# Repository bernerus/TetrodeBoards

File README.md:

# TetrodeBoards
The Tetrode Boards by Ian White, GM3SEK. Redesigned with KiCad.

In 1998 Ian White, G3SEK, nowadays GM3SEK designed control and protection circuits for RF power amplifiers
that use tube tetrodes. These boards were sold for many years by the designer but were retired around 2017
and are no longer available.

The manuals are still available however, and that documantation is excellent. 

After my retirement as a system developer I found time to return to the VHF DXing that I used to do as a 
student in the late 1970's.
By then one of the things I built was a VHF power amplifier, described by Fred Merry, W2GN, which was used
even for some EME contacts until around 1987 when a storm took my antenna. Since then, the amplifier was
only used occasionally.

Now, 37 years later, the ham world has changed quite a lot. Nowadays computers make the waveforms and almost
every ham has a spectrum analyzer built into their radio. My signals from the old PA didn't look very good there.

Actually it is probaly at miracle that the PA and its power supply worked at all now. There were lots of electrolytic
capacitors in the power supply that were surplus already in the mid 1970's, and when I got reports on hum on my
signal, I checked these caps. I had only about 8 uF left and the G1 and G2 voltage varied too much to be happy with.

That's when I found out that these tetrode boards could help, but since the boards were no longer sold, I decided
to try to re-engineer them using KiCad. This time using methods available today. Thus this design uses SMD mounted
components and professionally produced boards. I have some boards left, so anyone who likes to try building on these
boards can have them for the expense of postage. Beware though that they have issues. Check the issues tab at GitHub first.

A crucial component in Ian's design is the 748 op amp. 
These are no longer manufactured, but they are available at eBay.
Luckily for me, I found a few 748 IC:s leftover from the happy '70s in my old junkbox. 

Christer Bernérus, SM6FBQ. 
JO67BQ 2024-04-04.

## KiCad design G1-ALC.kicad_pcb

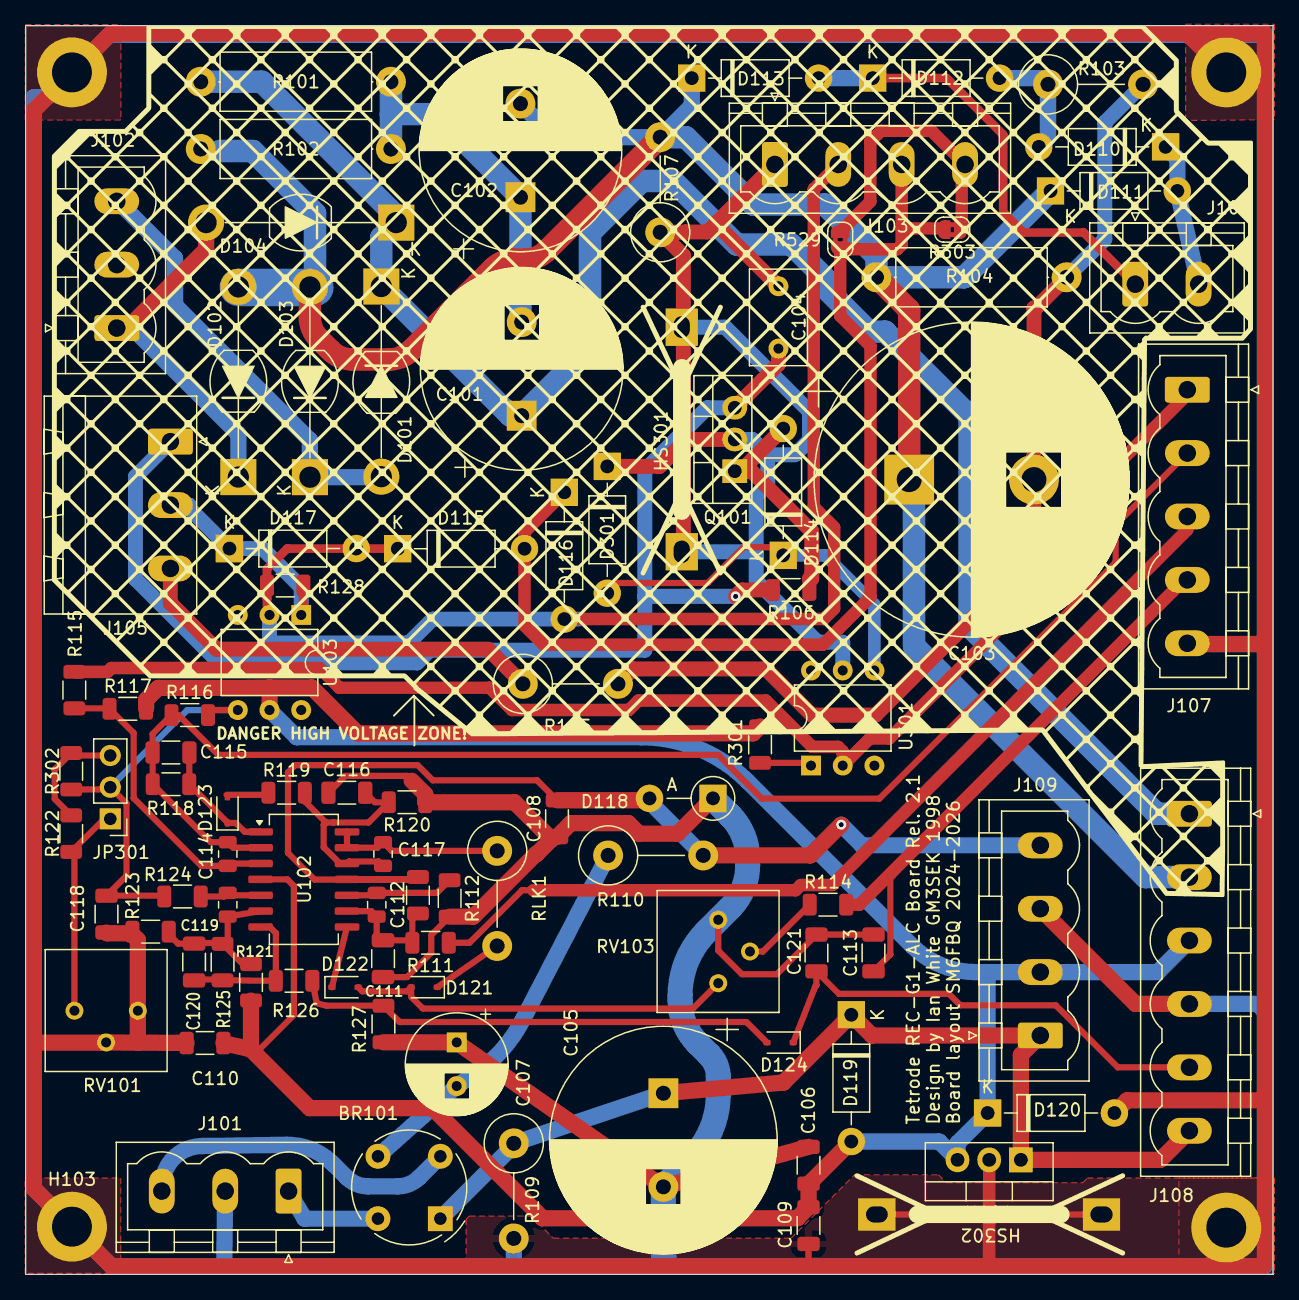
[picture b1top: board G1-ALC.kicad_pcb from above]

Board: 2 copper layers, 100.0 x 100.1 mm, 96 parts (0 on the bottom side), 49 nets.

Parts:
BR101: 2W06; Diode_Bridge_Round_D9.0mm
C101, C102: 100u 350V; CP_Radial_D16.0mm_P7.50mm
C103: 220u 200V; CP_Radial_D25.0mm_P10.00mm_SnapIn
C104: 100n 100V; C_Disc_D7.5mm_W4.4mm_P5.00mm
C105: 4m7 35V; CP_Radial_D18.0mm_P7.50mm
C106, C108, C109, C110, C111, C113, C115, C118, C120, C121: 100n; C_1206_3216Metric
C107: 100u 35V; CP_Radial_D8.0mm_P3.50mm
C112, C114, C117, C119: 33p; C_0805_2012Metric
C116: 1u; C_1206_3216Metric
D101, D102, D103, D104: BY228; D_SOD-64_P15.24mm_big_holes_Horizontal
D110, D111, D112, D113, D115, D116, D117, D119, D120: 1N4007; D_DO-41_SOD81_P10.16mm_Horizontal
D114: BZX85C56; D_DO-41_SOD81_P10.16mm_Horizontal
D118: BZX55C12V; D_DO-41_SOD81_P5.08mm_Vertical_AnodeUp
D121, D122, D123, D124: 1N4148WS; D_SOD-323
D301: 1N5365 36V; D_DO-41_SOD81_P10.16mm_Horizontal
H101, H102, H103, H104: MountingHole_Pad; MountingHole_3.2mm_M3_DIN965_Pad
HS301, HS302: Heatsink_Pad_2Pin; 6025DG_Cooler
J101: Conn_01x03_Pin; PhoenixContact_MSTBVA_2,5_3-G-5,08_1x03_P5.08mm_Vertical
J102: 330VAC; PhoenixContact_MSTBVA_2,5_3-G-5,08_1x03_P5.08mm_Vertical
J103, J109: G1 conn.; PhoenixContact_MSTBVA_2,5_4-G-5,08_1x04_P5.08mm_Vertical
J104: 105VAC in; PhoenixContact_MSTBVA_2,5_2-G-5,08_1x02_P5.08mm_Vertical
J105: Conn_01x03_Pin; PhoenixContact_MSTBA_2,5_3-G-5,08_1x03_P5.08mm_Horizontal
J107: Conn_01x05_Pin; PhoenixContact_MSTBVA_2,5_5-G-5,08_1x05_P5.08mm_Vertical
J108: G2 Control board interconnect; PhoenixContact_MSTBVA_2,5_6-G-5,08_1x06_P5.08mm_Vertical
JP301: ALC tune; PinHeader_1x03_P2.54mm_Vertical
Q101: TIP122; TO-220-3_Vertical
R101, R102, R104: 100k 2W; R_Axial_DIN0414_L11.9mm_D4.5mm_P15.24mm_Horizontal
R103: 1k5 2W; R_Axial_DIN0414_L11.9mm_D4.5mm_P7.62mm_Vertical
R105: 3k3 2W; R_Axial_DIN0414_L11.9mm_D4.5mm_P7.62mm_Vertical
R106, R122: 470R; R_1206_3216Metric
R107, R109: 4k7 2W; R_Axial_DIN0414_L11.9mm_D4.5mm_P7.62mm_Vertical
R110: 470R 1W; R_Axial_DIN0414_L11.9mm_D4.5mm_P7.62mm_Vertical
R111, R112, R115, R116, R121, R124: 10k; R_1206_3216Metric
R113: 100k; R_1206_3216Metric
R114: 100R; R_1206_3216Metric
R117, R118, R125: 470k; R_1206_3216Metric
R119: 2k7; R_1206_3216Metric
R120: 1M; R_1206_3216Metric
R123, R128: 22k; R_1206_3216Metric
R126: 39k; R_1206_3216Metric
R127: 33k; R_1206_3216Metric
R301: 270R; R_1206_3216Metric
R302: 560R; R_1206_3216Metric
R303, R529: 0; SolderJumper-2_P1.3mm_Bridged2Bar_RoundedPad1.0x1.5mm
RLK1: 0R; R_Axial_DIN0414_L11.9mm_D4.5mm_P7.62mm_Vertical
RV101: 1k; Potentiometer_Bourns_3386P_Vertical
RV103: 10k; Potentiometer_Bourns_3386P_Vertical
U101: LM7812_TO220; TO-220-3_Vertical
U102: LM324; SO-14_5.3x10.2mm_P1.27mm
U103: MCT5211M; DIP-6_W7.62mm
U301: CNY17-4; DIP-6_W7.62mm

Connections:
+12V: C106.1, C109.1, C110.1, D119.2 (A), D120.1 (K), J108.3, J109.2, R117.2, R121.2, R301.1, U101.3 (VO), U102.4 (V+), U103.5
+24V Unreg: BR101.1 (+), C105.1, D119.1 (K), J108.6, J109.1, R109.1, U101.1 (VI)
-12V: C108.2, D118.2 (A), J109.4, R110.2, R113.1, U102.11 (V-)
/18 VAC +: BR101.4, J101.1
/18 VAC -: BR101.2, J101.3
/105 VAC +: D112.1 (K), D113.2 (A), J104.1
/105 VAC -: D110.1 (K), D111.2 (A), J104.2
/330VAC +: D102.1 (K), D104.2 (A), J102.1
/330VAC -: D101.2 (A), D103.1 (K), J102.3
/ALC: C113.1, J107.4, R114.2
/Cathode: C102.2, C103.1, D102.2 (A), D103.2 (A), D111.1 (K), D113.1 (K), J108.2, R102.2, R104.1, R107.2
/Class AB1_L: J107.1, R115.1, U301.2
/G1: J103.4, R303.1, R529.1
/G1 Switch: C104.1, D301.1 (K), HS301.1, HS301.2, J103.1, Q101.2 (C), R107.1, U301.5
/G1 meter +: D115.1 (K), D116.2 (A), D117.2 (A), J103.2, R128.1, U103.2
/G1 meter -: D115.2 (A), D116.1 (K), J103.3, R303.2, R529.2
/G1 trip: C121.2, D124.1 (K), J108.5
/G2 Unreg: C101.1, D101.1 (K), D104.1 (K), J108.1, R101.1
/Ig1: C114.2, C115.1, J107.2, R116.1, R118.1, U102.2 (-)
/Inhibit: J107.3, R111.1
/RV102 Cold: C104.2, J105.1, Q101.3 (E), R106.2
/RV102 Hot: J105.3, R105.1
/RV102 Mid: D117.1 (K), J105.2, R128.2, U103.1
GND: C105.2, C106.2, C107.1, C108.1, C109.2, C110.2, C111.2, C113.2, C116.1, C118.2, C121.1, D118.1 (K), D120.2 (A), H101.1, H102.1, H103.1, H104.1, HS302.1, HS302.2, J101.2, J107.5, J108.4, J109.3, R109.2, R112.2, R120.1, R123.1, R127.1, RV101.2, RV101.3, RV103.3, U101.2 (GND)
unnamed: BR101.3 (-), C107.2, R110.1
unnamed: C101.2, C102.1, R101.2, R102.1
unnamed: C103.2, R103.2, R104.2, R105.2
unnamed: C120.2, R125.2, R126.1, U102.7
unnamed: D110.2 (A), D112.2 (A), R103.1
unnamed: D114.2 (A), Q101.1 (B), R106.1
unnamed: D114.1 (K), D301.2 (A), U301.4
unnamed: D121.2 (A), D122.2 (A), RV103.1
unnamed: D121.1 (K), RLK1.2
unnamed: D122.1 (K), U102.8
unnamed: D123.2 (A), R119.1
unnamed: C115.2, D123.1 (K), R118.2, U102.1
unnamed: D124.2 (A), R126.2, R127.2
unnamed: JP301.1 (A), R122.2, RV101.1
unnamed: JP301.3 (B), R122.1, R302.2
unnamed: C118.1, JP301.2 (C), R116.2, R124.1, R302.1, U103.4
unnamed: R114.1, RV103.2
unnamed: R301.2, U301.1
unnamed: C114.1, R115.2, R117.1, U102.3 (+)
unnamed: C119.1, R124.2, U102.5 (+)
unnamed: C119.2, C120.1, R121.1, R123.2, R125.1, U102.6 (-)
unnamed: C112.1, R112.1, U102.10 (+)
unnamed: C111.1, C112.2, R111.2, R113.2, U102.9 (-)
unnamed: C116.2, C117.1, R119.2, R120.2, U102.12 (+)
unnamed: C117.2, RLK1.1, U102.13 (-), U102.14

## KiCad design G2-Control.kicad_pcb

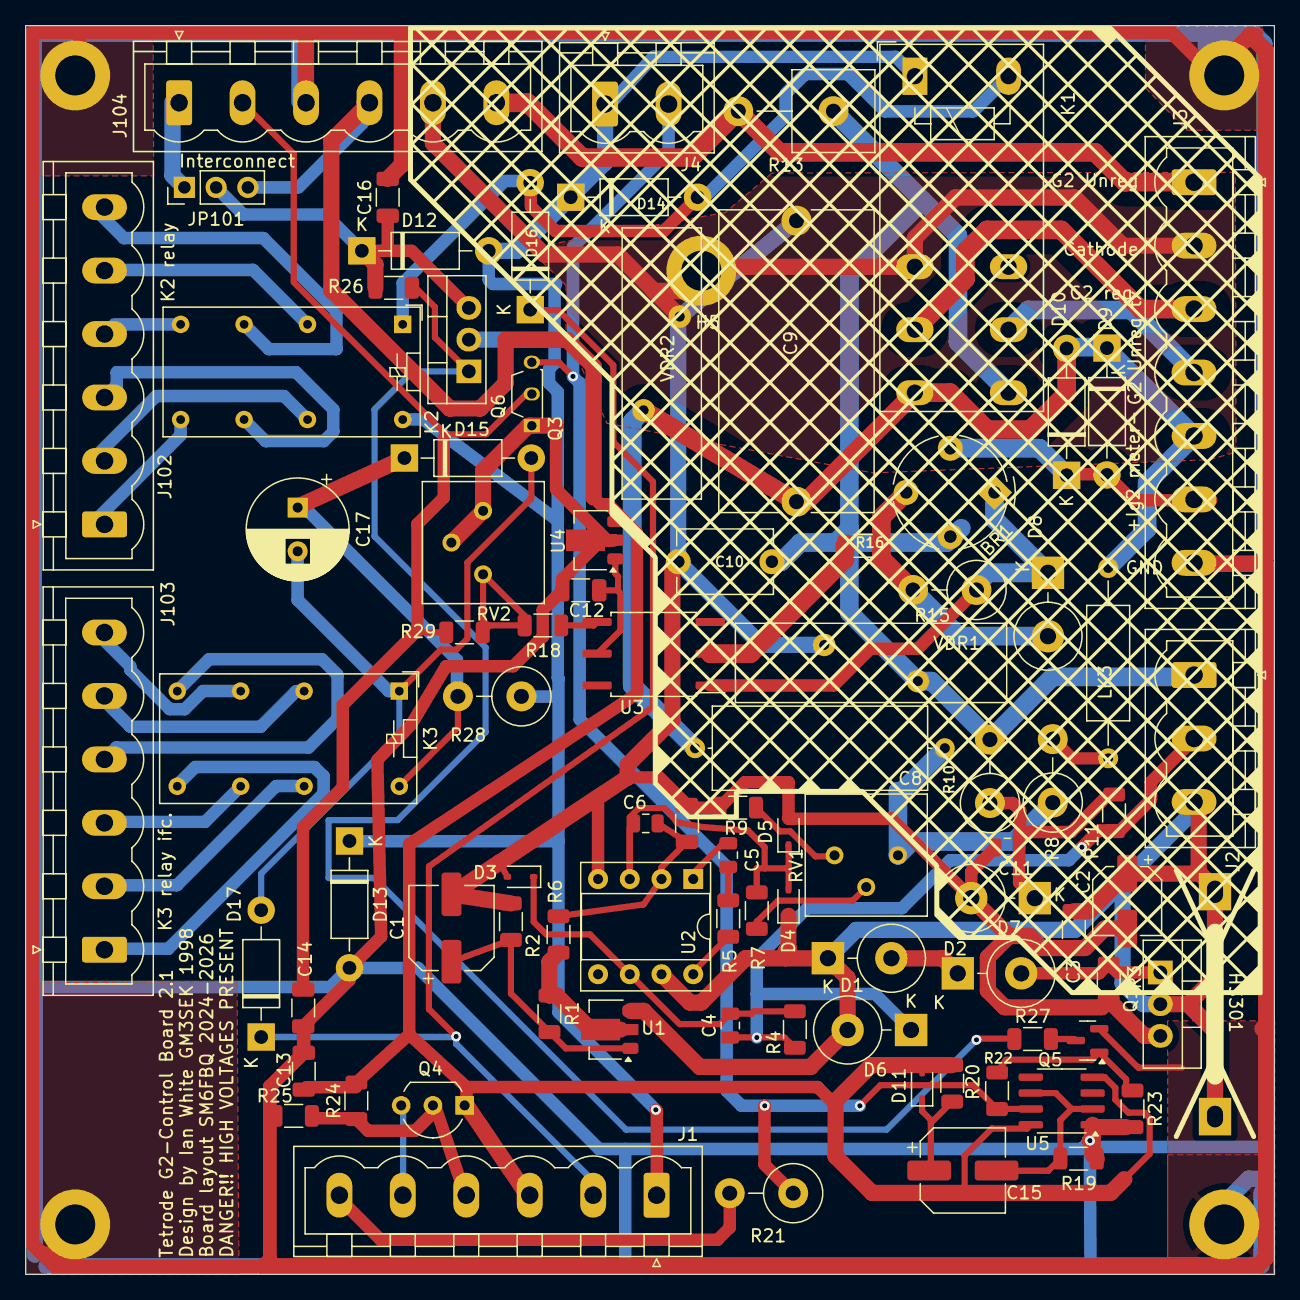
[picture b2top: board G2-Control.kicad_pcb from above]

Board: 2 copper layers, 100.0 x 100.0 mm, 93 parts (0 on the bottom side), 61 nets.

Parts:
BR1: 2W06; Diode_Bridge_Round_D9.0mm
C1, C15: 100u 16V; CP_Elec_6.3x5.7
C2: 10u 50V; CP_Elec_5x5.4
C3, C7, C13, C14, C16: 100n; C_1206_3216Metric
C4: 10n; C_0805_2012Metric
C5, C6: 33p; C_0805_2012Metric
C8: 4n7 630V; C_Axial_L17.0mm_D6.5mm_P20.00mm_Horizontal
C9: 100n 1kV; C_Rect_L24.0mm_W12.2mm_P22.50mm_MKT
C10: 10n 1kV; C_Disc_D7.5mm_W5.0mm_P7.50mm
C11: 470n; C_0805_2012Metric
C12: 10u; C_1206_3216Metric
C17: 100u 50V*; CP_Radial_D8.0mm_P3.50mm
D1, D2: BZX55C15V; D_DO-201_P5.08mm_Vertical_KathodeUp
D3, D4, D5, D11: 1N4148WS; D_SOD-323
D6: BZX55C12V; D_DO-201_P5.08mm_Vertical_KathodeUp
D7: BZT03C82; D_DO-201_P5.08mm_Vertical_KathodeUp
D8: 1N5337B; D_DO-201_P5.08mm_Vertical_KathodeUp
D9, D10, D12, D13, D14, D15, D16, D17: 1N4007; D_DO-41_SOD81_P10.16mm_Horizontal
H1, H2, H3, H4, H5: MountingHole_Pad; MountingHole_3.2mm_M3_DIN965_Pad
HS301: Heatsink_Pad_2Pin; 6025DG_Cooler
J1, J102, J103: Conn_01x06_Pin; PhoenixContact_MSTBVA_2,5_6-G-5,08_1x06_P5.08mm_Vertical
J2: Q2_link; PhoenixContact_MSTBVA_2,5_3-G-5,08_1x03_P5.08mm_Vertical
J3: Conn_01x07_Pin; PhoenixContact_MSTBVA_2,5_7-G-5,08_1x07_P5.08mm_Vertical
J4: Conn_01x05_Pin; PhoenixContact_MSTBVA_2,5_2-G-5,08_1x02_P5.08mm_Vertical
J104: Board Interconnect; PhoenixContact_MSTBVA_2,5_6-G-5,08_1x06_P5.08mm_Vertical
JP101: Relay voltage; PinHeader_1x03_P2.54mm_Vertical
K1: Schrack RTE24024; Relay_DPDT_Schrack-RT2-FormC_RM5mm
K2, K3: AZ822-2C-24DSE; Relay_DPDT_Omron_G5V-2
LK3: Jumper_2_Bridged; R_Axial_DIN0309_L9.0mm_D3.2mm_P15.24mm_Horizontal
Q1: TIP122; TO-220-3_Vertical
Q3: 2N5061; TO-92S_Wide
Q4: 2N4403; TO-92_Inline_Wide
Q5: BC847; SOT-23
Q6: IRF9530N; TO-220-3_Vertical
R1: 270R; R_1206_3216Metric
R2: 4k7; R_1206_3216Metric
R3: 470R; R_1206_3216Metric
R4: 39k; R_1206_3216Metric
R5: 2k7; R_1206_3216Metric
R6, R7: 22k; R_1206_3216Metric
R8: 470k 1W; R_Axial_DIN0414_L11.9mm_D4.5mm_P5.08mm_Vertical
R9: 27k*; R_1206_3216Metric
R10: 150k 1W*; R_Axial_DIN0414_L11.9mm_D4.5mm_P5.08mm_Vertical
R11: 82k; R_1206_3216Metric
R13: 10k 2W*; R_Axial_Power_L20.0mm_W6.4mm_P7.62mm_Vertical
R15: 120R 1W*; R_Axial_DIN0414_L11.9mm_D4.5mm_P5.08mm_Vertical
R16: 820R*; R_1206_3216Metric
R18: 220R; R_1206_3216Metric
R19: 330k*; R_1206_3216Metric
R20: 100k; R_1206_3216Metric
R21: 470R 1W; R_Axial_DIN0414_L11.9mm_D4.5mm_P5.08mm_Vertical
R22, R23, R24, R25, R26, R27, R29: 10k; R_1206_3216Metric
R28: 680 1W*; R_Axial_DIN0414_L11.9mm_D4.5mm_P5.08mm_Vertical
RV1: 10k; Potentiometer_Bourns_3386P_Vertical
RV2: 500R; Potentiometer_Bourns_3386P_Vertical
U1: LM317L_SOT89; SOT-89-3
U2: uA748; DIP-8_W7.62mm_Socket
U3: 4N36; SOP-6_6.62x6.62mm_P2.54mm
U4: 78L05; SOT-89-3
U5: LMC555CMX; SOIC-8_3.9x4.9mm_P1.27mm
VDR1, VDR2: V320LA40B*; RV_Disc_D21.5mm_W6.1mm_P7.5mm

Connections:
+5V: C12.1, U3.5, U4.1 (OUT)
+12V: C13.1, D11.2 (A), J1.3, J104.4, JP101.3 (B), Q4.1 (E), R20.2, R24.2, U4.3 (IN), U5.4 (R), U5.8 (VCC)
/24V Unreg: J104.1, JP101.1 (A)
/+30V rail: C2.1, C3.1, D1.1 (K), D4.1 (K), D6.2 (A), HS301.1, HS301.2, J2.3, Q1.2 (C), U1.3 (VI), U2.7 (V+)
/+Ig2: BR1.2, D9.2 (A), D10.1 (K), J3.6
/-Ig2: C8.2, C9.1, D9.1 (K), D10.2 (A), J3.5, K1.14, LK3.2 (B), VDR2.1
/AUX_TRIP_L: J4.2, Q3.3 (A), R21.1, R22.1, U5.7 (DIS)
/Alarm LED +: J1.5, Q4.3 (C)
/Alarm LED -: J1.6, R21.2
/CATHODE: C1.2, C2.2, C3.2, C7.2, C9.2, C10.2, C11.2, D3.2 (A), D5.2 (A), D7.2 (A), H5.1, J3.2, J104.5, K1.12, Q1.3 (E), R2.1, R3.1, R9.1, U2.4 (V-), VDR1.2, VDR2.2
/G1 trip: C14.1, J104.2, Q3.2 (G), R29.2
/G2 UNREG TX: J3.4, K1.21
/G2 Unreg: J3.1, J104.6, R13.2
/G2 reg: J3.3, K1.11
/HV Enable: D12.2 (A), D13.1 (K), D14.1 (K), J1.1, J4.1, K1.A1, K2.16, Q6.2 (D), R28.1
/K2B_NC: J102.6, K2.6
/K2B_NO: J102.4, K2.8
/K2B_com: J102.5, K2.4
/K2C_NC: J102.3, K2.11
/K2C_NO: J102.1, K2.9
/K2C_com: J102.2, K2.13
/K3B_NC: J103.6, K3.6
/K3B_NO: J103.4, K3.8
/K3B_com: J103.5, K3.4
/K3C_NC: J103.3, K3.11
/K3C_NO: J103.1, K3.9
/K3C_com: J103.2, K3.13
/PTT_L: D16.1 (K), D17.1 (K), J1.2
/Q2G: C4.1, D6.1 (K), J2.2, R4.2, R11.1
/R12: BR1.4, C10.1, J2.1, K1.24, R10.2, R13.1, VDR1.1
/Reset -: J1.4, Q4.2 (B), R24.1, R25.2
GND: C12.2, C13.2, C14.2, C16.2, D13.2 (A), H1.1, H2.1, H3.1, H4.1, J3.7, J104.3, Q3.1 (K), Q5.2 (E), R19.2, R23.2, R25.1, RV2.1, RV2.2, U4.2 (GND), U5.1 (GND)
unnamed: BR1.1 (+), D8.1 (K), R15.1, U3.1
unnamed: BR1.3 (-), D8.2 (A), R15.2, R16.2
unnamed: C5.1, R5.1
unnamed: C5.2, U2.1 (NULL)
unnamed: C8.1, R8.1, RV1.3
unnamed: D1.2 (A), D2.1 (K)
unnamed: D2.2 (A), Q1.1 (B), R3.2
unnamed: C4.2, D3.1 (K), R4.1, U2.6
unnamed: C6.1, D4.2 (A), D5.1 (K), R7.2, U2.3 (+)
unnamed: C11.1, D7.1 (K), R10.1, R11.2
unnamed: C15.1, D11.1 (K), R20.1
unnamed: C16.1, D12.1 (K), JP101.2 (C), Q6.3 (S), R26.1
unnamed: D14.2 (A), D16.2 (A), K1.A2, K2.1
unnamed: C17.2, D15.2 (A), D17.2 (A), K3.1
unnamed: C17.1, D15.1 (K), K3.16, R28.2
unnamed: LK3.1 (A), R8.2
unnamed: Q5.1 (B), R22.2, R23.1
unnamed: Q5.3 (C), R27.2
unnamed: Q6.1 (G), R26.2, R27.1
unnamed: R7.1, RV1.2
unnamed: R9.2, RV1.1
unnamed: R16.1, U3.2
unnamed: R18.1, R29.1, RV2.3
unnamed: R18.2, U3.4
unnamed: C1.1, R1.2, R2.2, U1.1 (ADJ)
unnamed: R1.1, R6.1, U1.2 (VO)
unnamed: C6.2, C7.1, R6.2, U2.2 (-)
unnamed: R5.2, U2.8 (FC)
unnamed: C15.2, R19.1, U5.2 (TR), U5.6 (THR)

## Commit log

2024-04-04 Update README.md
    Added the background story.
2024-04-04 Initial commit.
    This is the initial commit putting my Kicad design for the tetrode boards
    oroginally desigend by Ian White GM3SEK in 1998.
    This commit reflects the first version that was actually realized physically in 2024.
    Maybe more versions will come, maybe not.
2024-04-06 Update README.md
    Fixed typos.
2024-04-07 Fixes for issuees #1, €2 and #3
    Fixed unconnected capacitor and bleeder
    Turned connectors around to orient screw connectors with screws outward from the board.
    Use new footprint for BY228 diodes with larget pand and holes.
    Added a subsheet for notes containing differences with original drawing from GM3SEK.
2024-04-07 Fixes for issues #1, #2, #3 and #4
    Fixed unconnected capacitor and bleeder
    Turned connectors around to orient screw connectors with screws outward from the board.
    Use new footprint for BY228 diodes with larget pand and holes.
    Moved components to make more room for the Q101 heat sink.
    Cleared the top copper layer below the Q101 heat sink forn connected traces.
    Added a copper zone below the Q101 heat sink to make it possible to solder the heat sink onto the board.
2024-04-07 Added release number to the top silkscreen text.
2024-04-07 Fixes for issues #7 #6 #3 #5
    Connected U1 correctly.
    Added D6 to the board
    Added version number to silkscreen text.
    Added high voltage warning
    Turned Q1 around and moved it closer to the edge.
2024-04-07 Init commit.
2024-04-07 Umpdated notes subschematic.
2024-04-10 Fixed typos in README file.
    Added Testing.md file.
2024-04-14 Added a mounting hole below VDR2 and copper zones around to get a good grounding point for CATHODE when using the board for cathode grounded PA's. This is suggested in G3SEK's writeup "Power and Prot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
2024-04-14 Fix typos and update instructions in Testing.md
    A spelling mistake in the secondary winding section got corrected. Instructions for making connections between J108 on the G1-ALC board and J104 got clarified, including resistance check guidance. Ad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
2024-04-14 Update connector positions and routing in G1-ALC.kicad_pcb
    Repositioned two Phoenix Contact connectors in the PCB layout and rerouted the associated traces accordingly. Additionally rotated some properties at F.Fab layer to -90 degrees from the previous posi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
2024-04-14 Add new wiring and mounting hole to G2-Control schematic
    Introduced a mounting hole to the G2-Control KiCad. The hole is
    to be used as a low impedance connection between the CATHODE rail and chassis ground, in case of a cathode grounded PA.
    Otherwise the connection should be connected to the high tension negative pole.
2024-04-14 Update active layer and adjust circuit properties
2024-04-14 Added copper zones around the new CATHODE low impedance connection.
2024-04-14 Add DRC exclusions to G2-Control.kicad_pro
    Added numerous DRC exclusions to the G2-Control.kicad_pro file. Most of the added exclusions address the 'silk_over_copper' issue, limiting potential errors and collisions. Keeping these exclusions r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
2024-04-16 Cleaned up the G2-Control schematic.
    Removed Netclass names from their flags and greyed the flags so thet they
    interfere less with the actual schematic.
    Moved things around to avoid collisions.
    Moved D6 into the on-board space and shrunk the cutout for R12 and Q2
    Moved BR1 to get less parallel wirings for the same signal.
    Changed the SCR symbol in the library to make it more clear.
2024-04-16 Update component properties and positioning in PCB layout
    Several updates were made to the properties and positions of various components in the PCB layout file due to changes in the schematic.
    The Value property for numerous elements was changed, appending an asterisk at the end.
    Additionally, the Reference positions, Datasheet, and Description fields were modified for certain components.
2024-04-16 Update DRC exclusions in PCB files
    The list of DRC exclusions was updated due to changes in rules and design checks. Furthermore, the precise placement of elements on nets was altered to match the updated layout.
2024-05-04 Refine testing instructions and update component recommendations
    Significant modifications have been made to the testing instructions in 'Testing.md' for better understanding and accuracy. Additionally, changes in 'Changes_from_GM3SEK.md' included updated recommen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
2024-05-04 Updated junction positions and wire connections in schematic
    Performed major modifications to the junction positions and wire connections in the kicad schematic G1-ALC. The changes include removal and addition of certain junction points, repositioning of wires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
2024-05-04 Replaced Q4 transistor schematic symbol BC557 with 2N3904 in G2-Control schematic
    Updated the G2-Control schematic by replacing the schematic symbol BC557 for transistor Q4 with the symbol for 2N3904 which has the same pin numbering as the actual transistor used. This change fixes
    issue #11 and makes the silkscreen print on the PCB show the transistor the way it has to be rotated in order to function properly.
    Other changes is that the references and values of the components have been moved and the valye is set in a smaller font to increase readability. The global labels has also been replaced by hierarchi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
2024-05-04 The outputs of the comparators needed pullup resistors. Which have been added. This makes the ERV checker happier.
2024-05-04 Changed optocoupler U103 to a MCT5211
    The optocoupler U103 must be as sensitive as the MCT5211. It could not be replaced by CNY17-4 despite what is said by Mouser when searching for the MCT5211. Fortunately DigiKey has a direct replaceme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
2024-05-05 Cleanup schematic. No functional change.
    Replaced global labels with hierarchical.
    Consistent placement of references and values.
    Values typed in a smaller font.
2024-05-05 Moved cold end of R115 to CLASS_AB1_L instead of GND. The intent is to turn off ALC in case we want to run the PA in class C.
2024-05-06 Updated relay components and adjusted wiring
    The K1 relay has been updated from model AZ822-2C-24DSE to RTE24024 for better current handling in case of arc-over. Additionally, wiring for these components has been adjusted to fit the new model.
    Moved R13 to a better location and increased its footprint.
    Moved the grounding hole to a place near both the VDR2 and the connection to K1 in order to get as low as possible impedance to the cathode connection for these two components.
2024-05-06 Updated PCB layout to accommodate new relay model and reworked wiring
    Swapped existing Relay model with the Schrack-RT2 model, and updated PCB layout to accommodate the new output routes. Additionally, repositioned the Resistor R13 to ensure optimal grounding. This cha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
2024-05-06 Update DRC exclusions and active layer in PCB design
    Increased the number of DRC exclusions to accommodate new design rules in the G1-ALC.kicad_pro file.
2024-05-06 Updated capacitor C17. With the smaller relay and higher voltage, coil current is much less so 100 uF gives some 300-500 mS delay.
2024-09-14 Update Testing.md
    Update for version 2.0.0 of the boards.
    The connectors J107 and J108 of the G1 board has switched places and changed pin orders so the description from version 1 is no longer valid. More updates to come...
2024-09-23 Update Testing.md
    Fixed G1 switching paragraphs for vesrion 2.0
2024-09-23 Update Testing.md
    Clarified the G1 voltage power up section.
2024-09-24 Update Testing.md
    Changed pin 4 to pin 2 of J3
2024-09-24 Update Testing.md
    Updated for pin changes
2024-09-24 Update Testing.md
    More updates.
2024-09-24 Update Testing.md
    Typo fix
2024-09-24 Update Testing.md
    Added info on the scarcity of the 748. Fixed typo.
2024-09-24 Update Testing.md
    Updated the end.
2024-09-24 Added the ALC and G1 trip checks.
2024-09-26 Updated Testing.md
    Changed instructions regarding the ALC OUT checks.
2026-02-05 Fix typos and improve clarity in documentation.
2026-02-05 Updated format to KiCad 9. Included footprints etc.
    Standardized PCB layers, updated property formatting, and adjusted net assignments. Added some DigiKey, Electrokit, and Mouser component part numbers.
    Reduced font sizes for better readability and incorporated embedded font settings.
    Removed the sequencer from the schematic which wasn't really meant to be there.
    Revised and excluded drc and erc warnings and exclusions.
    Included footprints into the project library that formerly was defined outside of the project.
